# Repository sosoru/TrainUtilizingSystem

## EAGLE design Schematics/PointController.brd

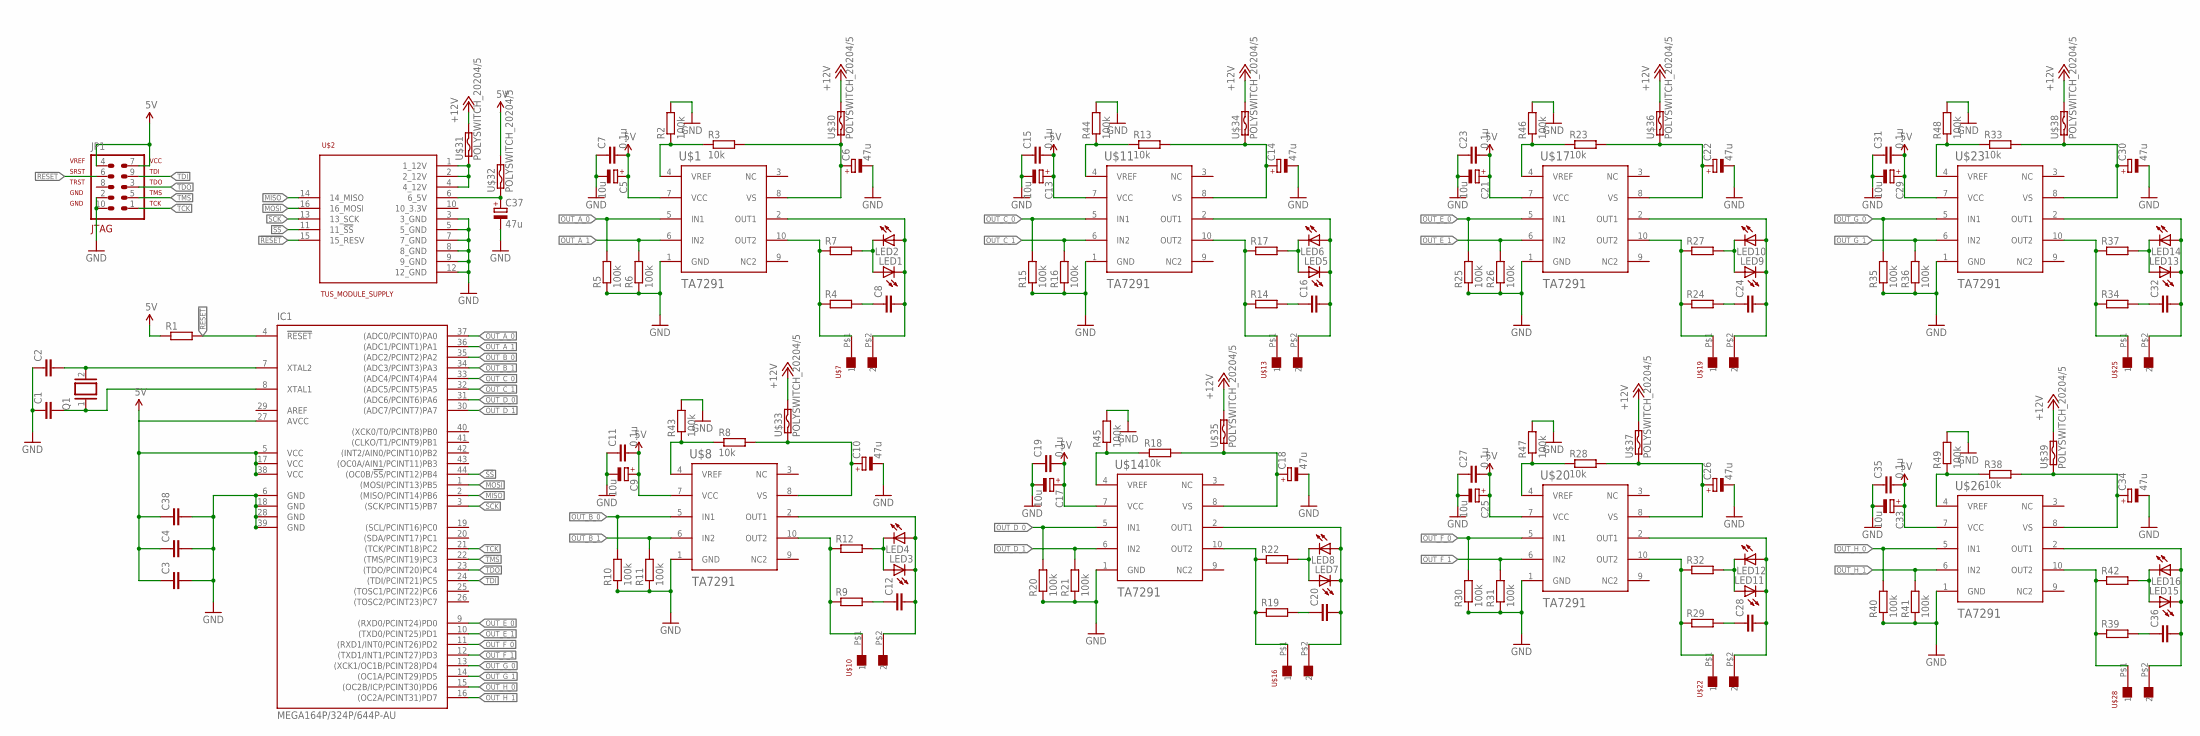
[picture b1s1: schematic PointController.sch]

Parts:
C1, C2, C3, C4, C38: C-EUC1608; C1608
C5, C9, C13, C17, C21, C25, C29, C33: 10u; E1,8-4
C6, C10, C14, C18, C22, C26, C30, C34, C37: 47u; E1,8-4
C7, C11, C15, C19, C23, C27, C31, C35: 0.1u; C1608
C8, C12, C16, C20, C24, C28, C32, C36: C5/3; C5B3
IC1: MEGA164P/324P/644P-AU; TQFP44
JP1: AVR-JTAG-10
LED1, LED2, LED3, LED4, LED5, LED6, LED7, LED8, LED9, LED10, LED11, LED12, LED13, LED14, LED15, LED16: LED3MM
Q1: XTAL/S; QS
R1: R-EU_R0603; R0603
R2, R5, R6, R10, R11, R15, R16, R20, R21, R25, R26, R30, R31, R35, R36, R40, R41, R43, R44, R45, R46, R47, R48, R49: 100k; R0603
R3, R8, R13, R18, R23, R28, R33, R38: 10k; R0603
R4, R7, R9, R12, R14, R17, R19, R22, R24, R27, R29, R32, R34, R37, R39, R42: R-EU_0204/7; 0204/7
U$1, U$8, U$11, U$14, U$17, U$20, U$23, U$26: TA7291; HSIP10
U$2: TUS_MODULE_SUPPLY; 2X08
U$7, U$10, U$13, U$16, U$19, U$22, U$25, U$28: XH-2
U$30, U$31, U$32, U$33, U$34, U$35, U$36, U$37, U$38, U$39: POLYSWITCH_20204/5; 0204/5

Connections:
5V: C3.1, C4.1, C5.+, C7.2, C9.+, C11.2, C13.+, C15.2, C17.+, C19.2, C21.+, C23.2, C25.+, C27.2, C29.+, C31.2, C33.+, C35.2, C38.1, IC1.5 (VCC), IC1.17 (VCC), IC1.27 (AVCC), IC1.38 (VCC), JP1.4, JP1.7, R1.1, U$1.7 (VCC), U$8.7 (VCC), U$11.7 (VCC), U$14.7 (VCC), U$17.7 (VCC), U$20.7 (VCC), U$23.7 (VCC), U$26.7 (VCC), U$32.2
!RESET: IC1.4 (!RESET), JP1.6, R1.2, U$2.15 (15_RESV)
!SS: IC1.44 ((OC0B/!SS!/PCINT12)PB4), U$2.11 (11_!SS)
+12V: U$30.2, U$31.2, U$33.2, U$34.2, U$35.2, U$36.2, U$37.2, U$38.2, U$39.2
AREF: IC1.29 (AREF)
GND: C1.1, C2.1, C3.2, C4.2, C5.-, C6.-, C7.1, C9.-, C10.-, C11.1, C13.-, C14.-, C15.1, C17.-, C18.-, C19.1, C21.-, C22.-, C23.1, C25.-, C26.-, C27.1, C29.-, C30.-, C31.1, C33.-, C34.-, C35.1, C37.-, C38.2, IC1.6 (GND), IC1.18 (GND), IC1.28 (GND), IC1.39 (GND), JP1.2, JP1.10, R2.2, R5.1, R6.1, R10.1, R11.1, R15.1, R16.1, R20.1, R21.1, R25.1, R26.1, R30.1, R31.1, R35.1, R36.1, R40.1, R41.1, R43.2, R44.2, R45.2, R46.2, R47.2, R48.2, R49.2, U$1.1 (GND), U$2.3 (3_GND), U$2.5 (5_GND), U$2.7 (7_GND), U$2.8 (8_GND), U$2.9 (9_GND), U$2.12 (12_GND), U$8.1 (GND), U$11.1 (GND), U$14.1 (GND), U$17.1 (GND), U$20.1 (GND), U$23.1 (GND), U$26.1 (GND)
MISO: IC1.2 ((MISO/PCINT14)PB6), U$2.14 (14_MISO)
MOSI: IC1.1 ((MOSI/PCINT13)PB5), U$2.16 (16_MOSI)
unnamed: LED1.A, LED2.K (C), R7.2
unnamed: R8.1, R43.1, U$8.4 (VREF)
unnamed: C1.2, IC1.8 (XTAL1), Q1.1
unnamed: C2.2, IC1.7 (XTAL2), Q1.2
unnamed: C12.2, LED3.K (C), LED4.A, U$8.2 (OUT1), U$10.P$2 (2)
unnamed: R2.1, R3.1, U$1.4 (VREF)
unnamed: C8.2, LED1.K (C), LED2.A, U$1.2 (OUT1), U$7.P$2 (2)
unnamed: R4.1, R7.1, U$1.10 (OUT2), U$7.P$1 (1)
unnamed: C8.1, R4.2
unnamed: R9.1, R12.1, U$8.10 (OUT2), U$10.P$1 (1)
unnamed: C12.1, R9.2
unnamed: LED3.A, LED4.K (C), R12.2
unnamed: R13.1, R44.1, U$11.4 (VREF)
unnamed: C16.2, LED5.K (C), LED6.A, U$11.2 (OUT1), U$13.P$2 (2)
unnamed: R14.1, R17.1, U$11.10 (OUT2), U$13.P$1 (1)
unnamed: C16.1, R14.2
unnamed: LED5.A, LED6.K (C), R17.2
unnamed: R18.1, R45.1, U$14.4 (VREF)
unnamed: C20.2, LED7.K (C), LED8.A, U$14.2 (OUT1), U$16.P$2 (2)
unnamed: R19.1, R22.1, U$14.10 (OUT2), U$16.P$1 (1)
unnamed: C20.1, R19.2
unnamed: LED7.A, LED8.K (C), R22.2
unnamed: R23.1, R46.1, U$17.4 (VREF)
unnamed: C24.2, LED9.K (C), LED10.A, U$17.2 (OUT1), U$19.P$2 (2)
unnamed: R24.1, R27.1, U$17.10 (OUT2), U$19.P$1 (1)
unnamed: C24.1, R24.2
unnamed: LED9.A, LED10.K (C), R27.2
unnamed: R28.1, R47.1, U$20.4 (VREF)
unnamed: C28.2, LED11.K (C), LED12.A, U$20.2 (OUT1), U$22.P$2 (2)
unnamed: R29.1, R32.1, U$20.10 (OUT2), U$22.P$1 (1)
unnamed: C28.1, R29.2
unnamed: LED11.A, LED12.K (C), R32.2
unnamed: R33.1, R48.1, U$23.4 (VREF)
unnamed: C32.2, LED13.K (C), LED14.A, U$23.2 (OUT1), U$25.P$2 (2)
unnamed: R34.1, R37.1, U$23.10 (OUT2), U$25.P$1 (1)
unnamed: C32.1, R34.2
unnamed: LED13.A, LED14.K (C), R37.2
unnamed: R38.1, R49.1, U$26.4 (VREF)
unnamed: C36.2, LED15.K (C), LED16.A, U$26.2 (OUT1), U$28.P$2 (2)
unnamed: R39.1, R42.1, U$26.10 (OUT2), U$28.P$1 (1)
unnamed: C36.1, R39.2
unnamed: LED15.A, LED16.K (C), R42.2
unnamed: U$2.1 (1_12V), U$2.2 (2_12V), U$2.4 (4_12V), U$31.1
unnamed: C37.+, U$2.6 (6_5V), U$32.1
unnamed: C6.+, R3.2, U$1.8 (VS), U$30.1
unnamed: C14.+, R13.2, U$11.8 (VS), U$34.1
unnamed: C22.+, R23.2, U$17.8 (VS), U$36.1
unnamed: C30.+, R33.2, U$23.8 (VS), U$38.1
unnamed: C34.+, R38.2, U$26.8 (VS), U$39.1
unnamed: C26.+, R28.2, U$20.8 (VS), U$37.1
unnamed: C18.+, R18.2, U$14.8 (VS), U$35.1
unnamed: C10.+, R8.2, U$8.8 (VS), U$33.1
OUT_A_0: IC1.37 ((ADC0/PCINT0)PA0), R5.2, U$1.5 (IN1)
OUT_A_1: IC1.36 ((ADC1/PCINT1)PA1), R6.2, U$1.6 (IN2)
OUT_B_0: IC1.35 ((ADC2/PCINT2)PA2), R10.2, U$8.5 (IN1)
OUT_B_1: IC1.34 ((ADC3/PCINT3)PA3), R11.2, U$8.6 (IN2)
OUT_C_0: IC1.33 ((ADC4/PCINT4)PA4), R15.2, U$11.5 (IN1)
OUT_C_1: IC1.32 ((ADC5/PCINT5)PA5), R16.2, U$11.6 (IN2)
OUT_D_0: IC1.31 ((ADC6/PCINT6)PA6), R20.2, U$14.5 (IN1)
OUT_D_1: IC1.30 ((ADC7/PCINT7)PA7), R21.2, U$14.6 (IN2)
OUT_E_0: IC1.9 ((RXD0/PCINT24)PD0), R25.2, U$17.5 (IN1)
OUT_E_1: IC1.10 ((TXD0/PCINT25)PD1), R26.2, U$17.6 (IN2)
OUT_F_0: IC1.11 ((RXD1/INT0/PCINT26)PD2), R30.2, U$20.5 (IN1)
OUT_F_1: IC1.12 ((TXD1/INT1/PCINT27)PD3), R31.2, U$20.6 (IN2)
OUT_G_0: IC1.13 ((XCK1/OC1B/PCINT28)PD4), R35.2, U$23.5 (IN1)
OUT_G_1: IC1.14 ((OC1A/PCINT29)PD5), R36.2, U$23.6 (IN2)
OUT_H_0: IC1.15 ((OC2B/ICP/PCINT30)PD6), R40.2, U$26.5 (IN1)
OUT_H_1: IC1.16 ((OC2A/PCINT31)PD7), R41.2, U$26.6 (IN2)
SCK: IC1.3 ((SCK/PCINT15)PB7), U$2.13 (13_SCK)
TCK: IC1.21 ((TCK/PCINT18)PC2), JP1.1
TDI: IC1.24 ((TDI/PCINT21)PC5), JP1.9
TDO: IC1.23 ((TDO/PCINT20)PC4), JP1.3
TMS: IC1.22 ((TMS/PCINT19)PC3), JP1.5

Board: 2 copper layers, 133 parts (0 on the bottom side), 80 nets, no tracks yet.
